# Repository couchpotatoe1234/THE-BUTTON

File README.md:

# THE-BUTTON
A Macropad with one singular button. Used for an emergency button to close a tab when a parent is coming perhaps...
The Button is a simple macropad, with a simple, 3D printed frame, and a PCB that can be hand soldered.

It features a big, red button that can be pressed to a custom function (cmd-w, cmd-tab, cmd-t). I made this as a my firs wireless project, and my first project with a programmable LED. The PCB itself is rather simple, featuring some capacitors, and on/off switch, the switch, led, and the microcontroller, the Seeed Xiao ESP32-C3.  The Seeed module was chosen because it has such a small and compact size. The board stackup will look something in the end like this: 
Onshape link: https://cad.onshape.com/documents/538be2b03248936ece9d33c1/w/1df8d390b01067d8bd89da4b/e/d1b17809ce85756e19fc8225?renderMode=0&uiState=69f60f8da8c5c45881890bfc
BOM:
| Name                          | Purpose                                 | Quantity | Total Cost (USD) | Link                                                                                                                                                                                                                                                                               | Distributor            |
|-------------------------------|-----------------------------------------|----------|------------------|------------------------------------------------------------------------------------------------------------------------------------------------------------------------------------------------------------------------------------------------------------------------------------|------------------------|
| 3D printed Parts              | The Case                                | 1        | 0.00             |                                                                                                                                                                                                                                                                                    | Anyone w/ a 3d printer |
| PCB                           | Where all the parts go on.              | 1        | 4.00             | https://jlcpcb.com                                                                                                                                                                                                                                                                 | JLCPCB                 |
| Cherry MX blue switch         | The main button                         | 1        | 1.75             | https://www.digikey.com/en/products/detail/cherry-americas-llc/MX2A-E1NB/21738397?gclsrc=aw.ds&gad_source=1&gad_campaignid=20243136172&gbraid=0AAAAADrbLlj5uJB4-UCn8Jcq0vyVTZ4ea&gclid=CjwKCAjwqazPBhALEiwAOuXqdCz_dlkZwhjgh_24bJ5zJWTk9k1aX59YHyKA8zXzAMtSSEA7STq8FBoCcMoQAvD_BwE | Digkikey               |
| WS2812B                       | The RGB LEDs, one extra because its SMD | 2        | 1.36             | https://www.digikey.com/en/products/detail/sparkfun-electronics/16347/11630204                                                                                                                                                                                                     | Digikey                |
| 100µF capacitor               | to stabilize voltage during WIFI peaks  | 1        | 0.45             | https://www.digikey.com/en/products/detail/nichicon/UPW1H101MPD/589640?gclsrc=aw.ds&gad_source=1&gad_campaignid=20228387720&gbraid=0AAAAADrbLlil683OaSPSESvxX-Ci8hL8c&gclid=CjwKCAjw46HPBhAMEiwASZpLRPG64ffxjeE-H9QIviqLggNZI-giQukbrM7XxPDN5vtHO0DAxoICaBoCgp0QAvD_BwE            | Digikey                |
| 1µF capacitor                 | To stabilize the LDO                    | 2        | 1.60             | https://www.digikey.com/en/products/detail/murata-electronics/RDER72A105K2M1H03A/4771353                                                                                                                                                                                           | Digikey                |
| 0.1µF capacitor               | for the LED                             | 1        | 0.28             | https://www.digikey.com/en/products/detail/vishay-beyschlag-draloric-bc-components/K104K15X7RF5TL2/286538                                                                                                                                                                          | Digikey                |
| 330Ω Resistor                 | For the LED                             | 1        | 0.10             | https://www.digikey.com/en/products/detail/stackpole-electronics-inc/CFM12JT330R/1741936                                                                                                                                                                                           | Digikey                |
| SPST slide switch             | for on & off-ing                        | 1        | 4.21             | https://www.digikey.com/en/products/detail/c-k/L101011ML04Q/3753550                                                                                                                                                                                                                | Digikey                |
| 3xAAA battery holder          | To hold the batteries                   | 1        | 1.79             | https://www.digikey.com/en/products/detail/keystone-electronics/2480/303825?gclsrc=aw.ds&gad_source=1&gad_campaignid=20243136172&gbraid=0AAAAADrbLlgQYe09PPf0O7EKtdKZZmIhf&gclid=CjwKCAjw46HPBhAMEiwASZpLRHULFnkGrp_fAm7Zs8xUfdqgpxbOTEhgJAsfNiPpHGBhjguWk6aUqRoCTKYQAvD_BwE       | Digikey                |
| Low Dropout Regulator MCP1700 | (1 extra) To control the voltage        | 2        | 1.00             | https://www.digikey.com/en/products/detail/microchip-technology/MCP1700-1202E-TO/651107                                                                                                                                                                                            | Digikey                |
| 7 pin headers                 | to connect the MCU to the PCB           | 2        | 0.20             | https://www.digikey.com/en/products/detail/adam-tech/PH1-07-UA/9830505                                                                                                                                                                                                             | Digikey                |
| Seeed Xiao Esp32-C3           | The MCU                                 | 1        | 4.99             | https://www.digikey.com/en/products/detail/seeed-technology-co-ltd/113991054/16652880                                                                                                                                                                                              | Digikey                |

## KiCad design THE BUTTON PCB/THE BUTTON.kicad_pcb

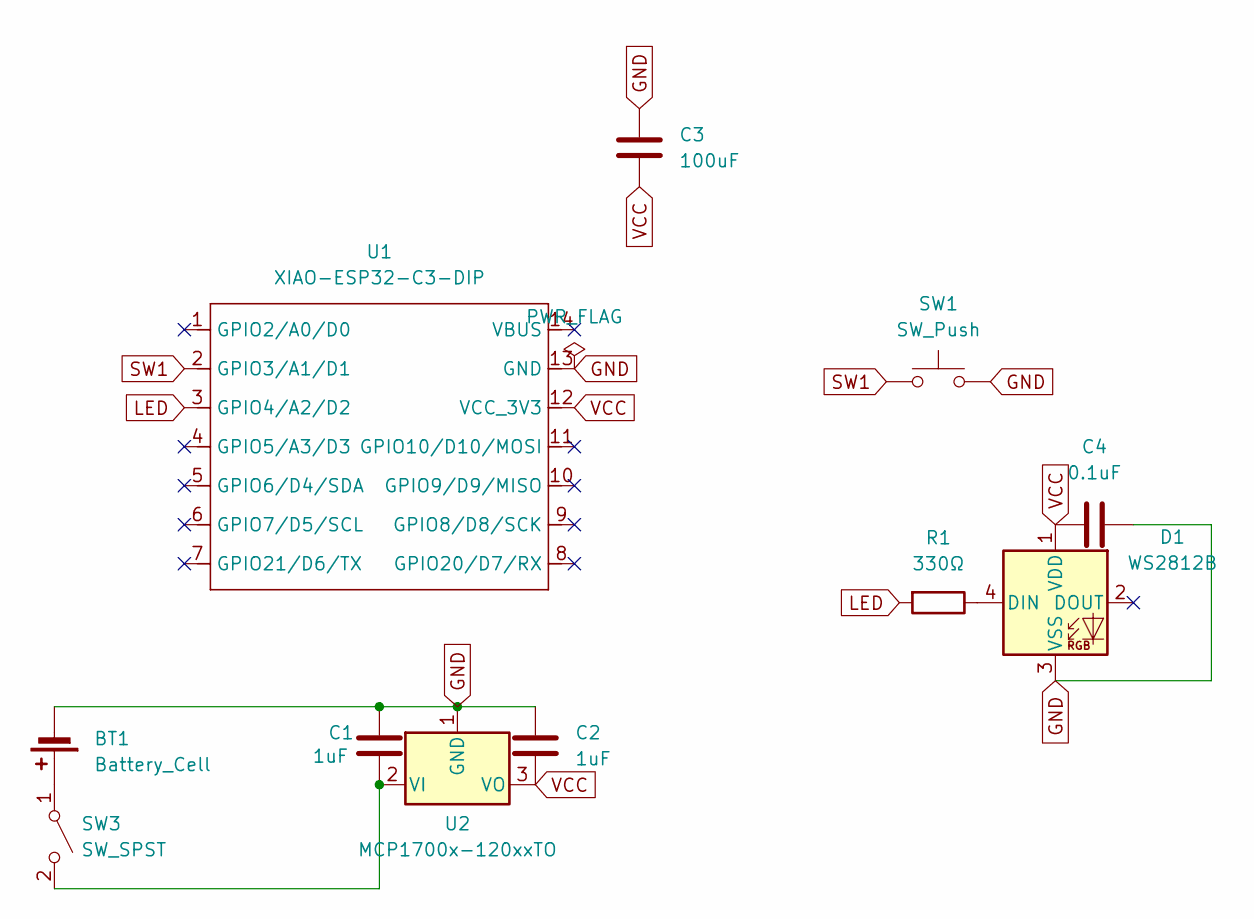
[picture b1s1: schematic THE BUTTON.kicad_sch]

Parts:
BT1: Battery_Cell; PinHeader_1x02_P2.54mm_Vertical
C1, C2: 1uF; C_Disc_D5.1mm_W3.2mm_P5.00mm
C3: 100uF; PCAP_8x11_5-THRU-ELECT_NCA
C4: 0.1uF; K104K15X7RF5TL2_VIS
D1: WS2812B; LED_WS2812B_PLCC4_5.0x5.0mm_P3.2mm
R1: 330Ω; R_Axial_DIN0207_L6.3mm_D2.5mm_P10.16mm_Horizontal
SW1: SW_Push; SW_Cherry_MX_1.00u_PCB
SW3: SW_SPST; SW3x1_L101011ML04Q_CNK
U1: XIAO-ESP32-C3-DIP
U2: MCP1700x-120xxTO; TO-92_Inline

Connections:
GND: BT1.2 (-), C1.1, C2.1, C3.1, C4.2, D1.3 (VSS), SW1.2, U1.13 (GND), U2.1 (GND)
LED: R1.2, U1.3 (GPIO4/A2/D2)
unnamed: BT1.1 (+), SW3.1 (A)
unnamed: D1.4 (DIN), R1.1
unnamed: C1.2, SW3.2 (B), U2.2 (VI)
SW1: SW1.1, U1.2 (GPIO3/A1/D1)
VCC: C2.2, C3.2, C4.1, D1.1 (VDD), U1.12 (VCC_3V3), U2.3 (VO)

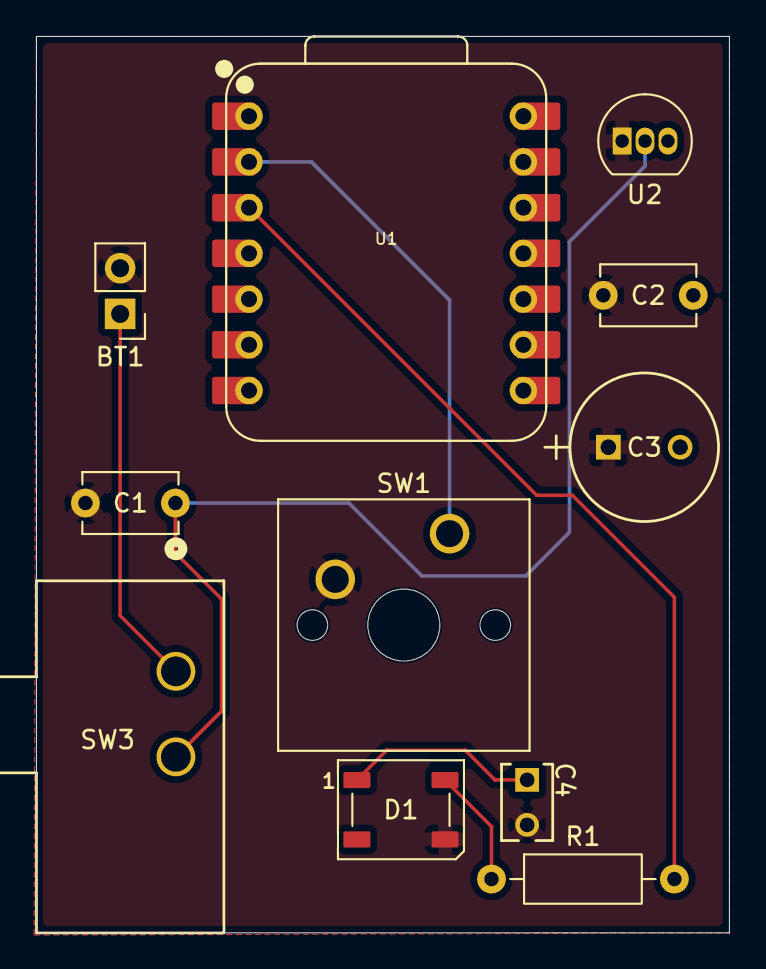
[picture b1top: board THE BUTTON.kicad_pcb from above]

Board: 2 copper layers, 38.5 x 49.8 mm, 11 parts (0 on the bottom side), 7 nets.

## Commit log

2026-04-26 adding PCB and BOM
2026-04-29 case & firmware
2026-05-02 case & README
2026-05-02 all parts
